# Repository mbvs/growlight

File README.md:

# growlight
An Arduino growing lights timer

The growlight is a time switch based on the DS3231 Precision RTC.
It allows setting of current time, on-time and off-time with buttons, displays time on a 4 digit 7 segment display and switches the state of the connected lights based on set on- and off times.
It also features a 3-way toggle switch to manually turn on and off the lights or pass control to the timer.

## Hardware

* Arduino nano
* DS3231 Precision RTC Module
* 4 digit 7 segment display with TM1637 controller
* 4 buttons
* ON-OFF-ON SPDT toggle switch
* IRLZ34 Logic level N-Channel MOSFet
* various resistors and leds

## Software

Growlight is developed in Visual Studio Code with the PlatformIO Plugin. To compile and flash connect your board to the PC, edit the platformio.ini upload_port setting to your needs and issue
the platformIO build and upload commands.

## TODO
* switch fet and button confirm pins for easier rooting (perhaps shift more pins around)

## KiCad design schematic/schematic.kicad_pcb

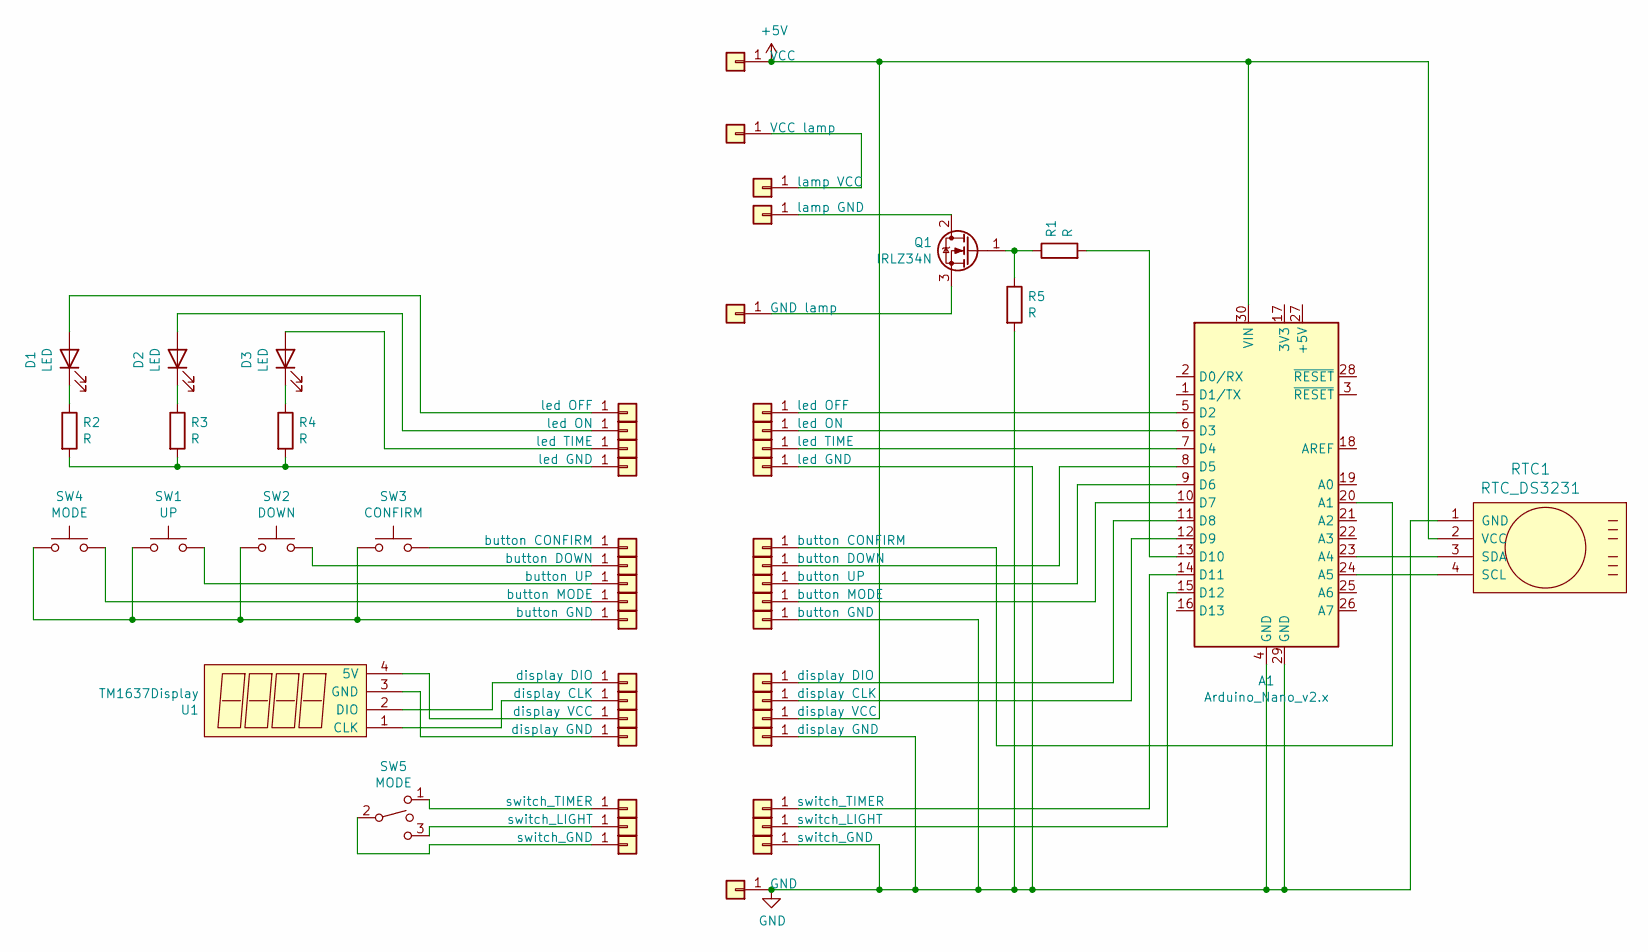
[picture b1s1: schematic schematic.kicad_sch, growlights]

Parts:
A1: Arduino_Nano_v2.x; Arduino_Nano
D1, D2, D3: LED; LED_D3.0mm
J1: lamp VCC; SolderWirePad_1x01_Drill0.8mm
J2: lamp GND; SolderWirePad_1x01_Drill0.8mm
J3, J16: led OFF; SolderWirePad_1x01_Drill0.8mm
J4, J17: led ON; SolderWirePad_1x01_Drill0.8mm
J5, J18: led TIME; SolderWirePad_1x01_Drill0.8mm
J6, J19: led GND; SolderWirePad_1x01_Drill0.8mm
J7, J20: button CONFIRM; SolderWirePad_1x01_Drill0.8mm
J8, J21: button DOWN; SolderWirePad_1x01_Drill0.8mm
J9, J22: button UP; SolderWirePad_1x01_Drill0.8mm
J10, J23: button MODE; SolderWirePad_1x01_Drill0.8mm
J11, J24: button GND; SolderWirePad_1x01_Drill0.8mm
J12, J25: display DIO; SolderWirePad_1x01_Drill0.8mm
J13, J26: display CLK; SolderWirePad_1x01_Drill0.8mm
J14, J27: display VCC; SolderWirePad_1x01_Drill0.8mm
J15, J28: display GND; SolderWirePad_1x01_Drill0.8mm
J29: VCC; SolderWirePad_1x01_Drill0.8mm
J30: VCC lamp; SolderWirePad_1x01_Drill0.8mm
J31: GND lamp; SolderWirePad_1x01_Drill0.8mm
J32: GND; SolderWirePad_1x01_Drill0.8mm
J33, J36: switch_TIMER; SolderWirePad_1x01_Drill0.8mm
J34, J37: switch_LIGHT; SolderWirePad_1x01_Drill0.8mm
J35, J38: switch_GND; SolderWirePad_1x01_Drill0.8mm
Q1: IRLZ34N; TO-220-3_Vertical
R1, R2, R3, R4, R5: R; R_Axial_DIN0207_L6.3mm_D2.5mm_P10.16mm_Horizontal
RTC1: RTC_DS3231
SW1: UP; SW_PUSH-12mm
SW2: DOWN; SW_PUSH-12mm
SW3: CONFIRM; SW_PUSH-12mm
SW4: MODE; SW_PUSH-12mm
SW5: MODE; SW_Toggle_Blue_wSlots
U1: TM1637Display; PinSocket_1x04_P2.54mm_Vertical

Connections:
+5V: A1.30 (VIN), J27.1, J29.1, RTC1.2 (VCC)
GND: A1.4 (GND), A1.29 (GND), J19.1, J24.1, J28.1, J32.1, J38.1, R5.2, RTC1.1 (GND)
unnamed: A1.5 (D2), J16.1
unnamed: A1.6 (D3), J17.1
unnamed: A1.7 (D4), J18.1
unnamed: A1.8 (D5), J21.1
unnamed: A1.9 (D6), J22.1
unnamed: A1.10 (D7), J23.1
unnamed: A1.11 (D8), J25.1
unnamed: A1.12 (D9), J26.1
unnamed: A1.13 (D10), R1.2
unnamed: A1.14 (D11), J36.1
unnamed: A1.15 (D12), J37.1
unnamed: A1.20 (A1), J20.1
unnamed: A1.23 (A4), RTC1.3 (SDA)
unnamed: A1.24 (A5), RTC1.4 (SCL)
unnamed: D1.1 (K), R2.1
unnamed: D1.2 (A), J3.1
unnamed: D2.1 (K), R3.1
unnamed: D2.2 (A), J4.1
unnamed: D3.1 (K), R4.1
unnamed: D3.2 (A), J5.1
unnamed: J1.1, J30.1
unnamed: J2.1, Q1.2 (D)
unnamed: J6.1, R2.2, R3.2, R4.2
unnamed: J7.1, SW3.2
unnamed: J8.1, SW2.2
unnamed: J9.1, SW1.2
unnamed: J10.1, SW4.2
unnamed: J11.1, SW1.1, SW2.1, SW3.1, SW4.1
unnamed: J12.1, U1.2 (DIO)
unnamed: J13.1, U1.1 (CLK)
unnamed: J14.1, U1.4 (5V)
unnamed: J15.1, U1.3 (GND)
unnamed: J31.1, Q1.3 (S)
unnamed: J33.1, SW5.1
unnamed: J34.1, SW5.3
unnamed: J35.1, SW5.2
unnamed: Q1.1 (G), R1.1, R5.1

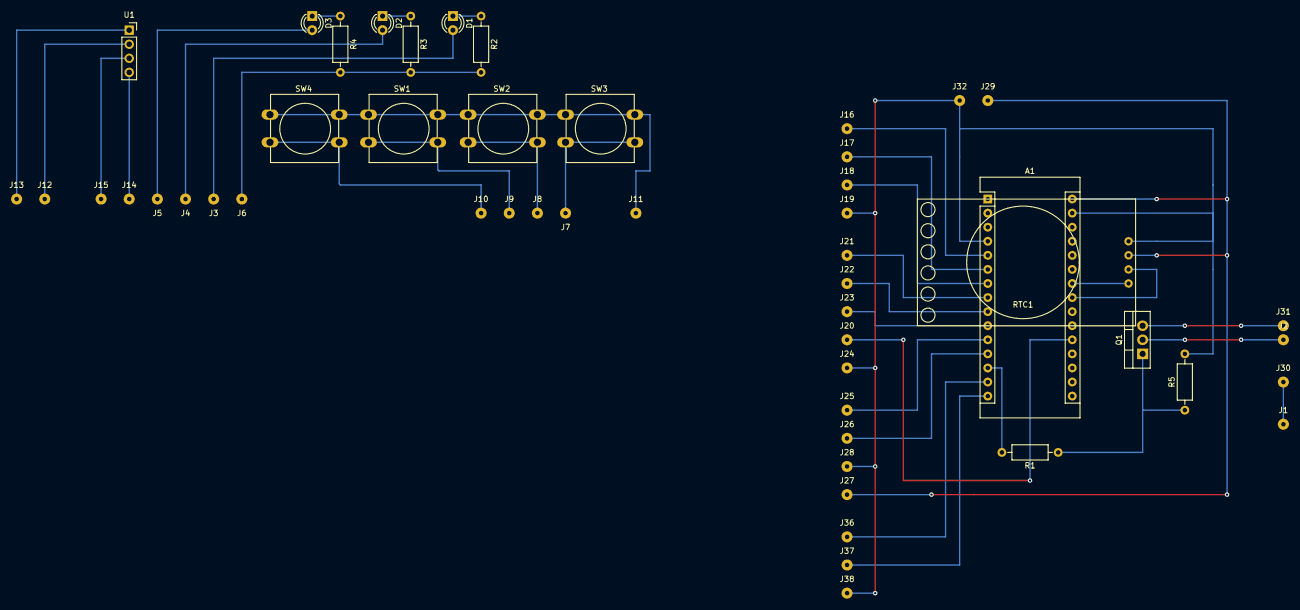
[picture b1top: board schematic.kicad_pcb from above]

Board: 2 copper layers, 51 parts (0 on the bottom side), 36 nets.

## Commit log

2021-03-09 update todos
2021-03-10 add lights modul
2021-03-10 add times persistence
2021-03-10 refactor light switching algorithm
2021-03-11 toggle temp time display
2021-03-11 dimm lights up and down
2021-03-12 add KiCad schematic
2021-03-15 add mode toggle switch
2021-03-15 setup confirm button
2021-03-15 stub out confirm routine
2021-03-16 implement set button
2021-03-20 add log dimming
2021-03-20 fix counting of dimm values
2021-03-20 draw schematics
2021-03-25 update board
2021-03-25 update TODO
2021-04-01 make arduino part of pcb
2022-03-27 update schematic to KiCad 6
